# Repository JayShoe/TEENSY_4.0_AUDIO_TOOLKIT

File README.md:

# Teensy 4.0 Audio Toolkit and Shield
Licensed under CC BY-NC-SA 4.0
https://creativecommons.org/licenses/by-nc-sa/4.0/
Project by Jay Shoemaker

*Project is incomplete, accepting feedback now!

The Teensy 4.0 Audio Toolkit and Shield is part of an open source project for learning about, designing, and rapid-prototyping custom Audio PCBs using the Teensy Audio Library. This kit exposes key features of the Teensy commonly used for audio including USB Host Input, MIDI In, Midi Out, Midi Through, SPDIF, and Toslink. The board also includes an SD Memory Card reader, RAM/Memory, and a Power Supply. Plus, the schematic points out the key pins for connecting your own audio chips to the Teensy. This project is just exposing the hardware. Some functions may require additional work on the Teensy Audio Library or your custom code.  

# Teensy Audio Toolkit and Shield's Key Features
 * Open Source CC BY-NC-SA 4.0
 * Stackable Design – To easily integrate with other stackable modules including DAC, ADC, Codec, Bluetooth, etc. 
 * Starting Point for Custom IO Panels – All inputs/outputs are only exposed as header pins. Use of a custom daughterboard, dongle, or soldering directly to the Audio Toolkit Mainboard to expose the desired jacks or ports. 
  * SD Card Reader  - via DM3D-SF Hirose Electric Co Ltd. 
  * Memory – via W25Q128JV, W25Q128FV, or 23LC1024 RAM. 
  * USB Host – via standard pinout USB Header and USB A connector and includes a TPS2055A current limiter chip. 
  * SPDIF Input and Output – via header, Coax, or Toslink.
  * MIDI In, Out, and Through – via header, DIN 5, or 3.5mm 3-pin Mini MIDI and includes an optocoupler (6N137) and a logic gate (74LS00) for proper termination. 
  * Power Supply – 1 Amp regulator for both 5V and 3.3V rails (LM2940) with an input voltage range of 6 V to 26 V. 
 * Footprints, 3d Models, and Schematics included. 
 * SAI Connectivity and Labels. The teensy footprint has been modified to include wide pads and pin information for standard I2S connectivity. Solder wire to those pads for an easy and secure connection to external DAC/ADC/CODEC/ETC. 
  * Master Clock - 100 Ohm resistors installed on MCLK1 and MCLK2 lines for easy connectivity. 
  * i2C - Pull up resistors on board for easy connectivity.
# Daughterboards with Jacks/Ports
The Audio Toolkit Shield’s header allows simple connections to one or more daughter boards. The mainboard and daughter board’s source and gerbers will be publicly available on the project repository. Pre-assembled boards will be made available (when tested/complete). Create your own daughterboard using the toolkit as a starting point. (Be sure to contribute back your modifications!)
## Designing a Custom Daughterboard
1.	Delete unneeded parts including the Audio Toolkit Mainboard. 
2.	Place and route your components. Define your edge cuts. Order your board. 
3.	Connect your customer IO Board to the Audio Toolkit Mainboard IO Header. 
## Audio Toolkit Notes
-	Use pre-built IO boards found within the project’s repository. 
-	Use the “Audio Toolkit IO Header” to stack your custom IO Board on top of the mainboard via the headers. 
-	Use the individual headers to create smaller custom IO Boards and link your project via ribbon cables, etc. 
-	Use the schematic to create your own entirely new custom Audio Toolkit or integrate it into your own project.

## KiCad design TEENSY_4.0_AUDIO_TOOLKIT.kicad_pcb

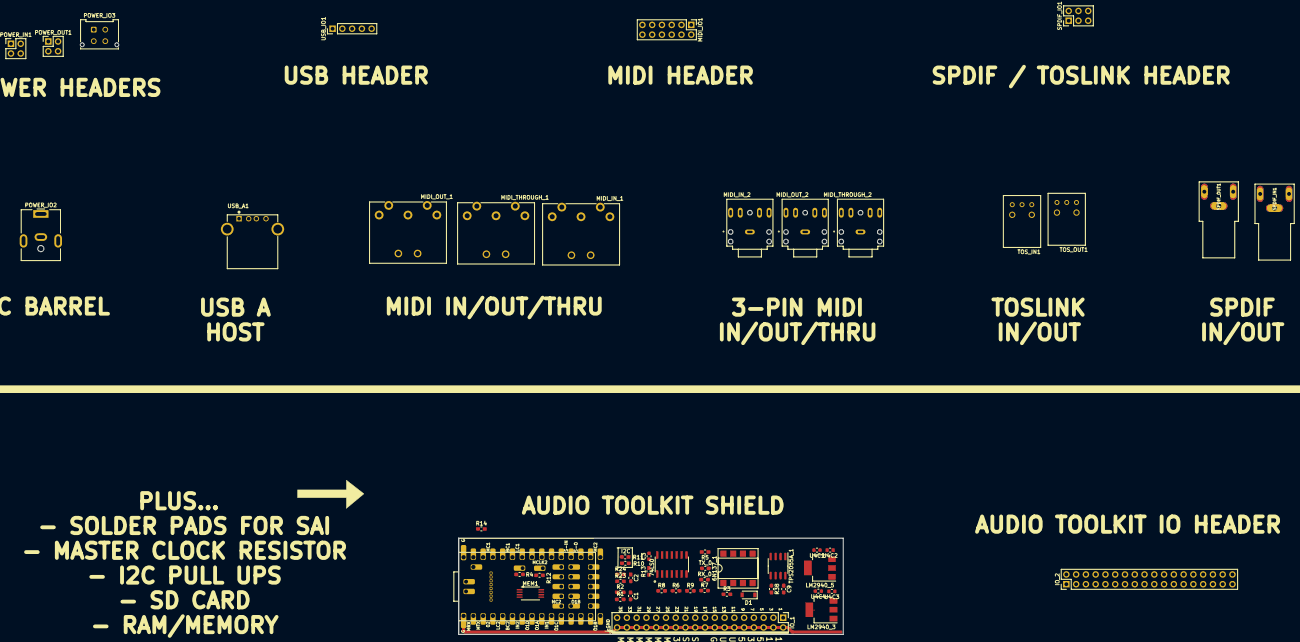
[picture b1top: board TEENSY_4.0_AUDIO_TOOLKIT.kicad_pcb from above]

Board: 2 copper layers, 100.0 x 25.0 mm, 58 parts (1 on the bottom side), 56 nets.

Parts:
6N137_1: 6N137; DIP-8_W7.62mm_SMDSocket_SmallPads
74LS0: 74LS00; 74LS00_SOIC127P600X175-14N
C1, C2: 1μ; C_0603_1608Metric_Pad1.05x0.95mm_HandSolder
C3: .1 uF; C_0603_1608Metric
C9: 100uf; C_0603_1608Metric_Pad1.05x0.95mm_HandSolder
D1: 1N4148; D_SOD-123
IO_1: IO_1; PinHeader_2x18_P2.54mm_Vertical
IO_2: IO_2; PinHeader_2x18_P2.54mm_Vertical
LM2940_3: LM2940IMP-33; SOT-223
LM2940_5: LM2940IMP-5; SOT-223
MCLK1: MCLK1; SolderWirePad_1x01_THROUGH_SOLDER
MCLK2: MCLK2; SolderWirePad_1x01_THROUGH_SOLDER
MEM1: 23LC1024-I_P; 23LC1024
MIDI_IN_1: DIN-5; SDS-50J_MIDI_JACK
MIDI_IN_2: 35RAPC4BHN2; 3.5MM_SWITCHCRAFT_35RAPC4BHN2
MIDI_IO1: MIDI_IO1; PinHeader_2x06_P2.54mm_Vertical
MIDI_OUT_1: DIN-5; SDS-50J_MIDI_JACK
MIDI_OUT_2: 35RAPC4BHN2; 3.5MM_SWITCHCRAFT_35RAPC4BHN2
MIDI_THROUGH_1: DIN-5; SDS-50J_MIDI_JACK
MIDI_THROUGH_2: 35RAPC4BHN2; 3.5MM_SWITCHCRAFT_35RAPC4BHN2
POWER_IN1: Conn_02x02_Odd_Even; PinHeader_2x02_P2.54mm_Vertical
POWER_IO2: Barrel_Jack; BarrelJack_CUI_PJ-063AH_Horizontal
POWER_IO3: Microfit_power; Molex_Micro-Fit_3.0_43045-0412_2x02_P3.00mm_Vertical
POWER_OUT1: Conn_02x02_Odd_Even; PinHeader_2x02_P2.54mm_Vertical
R1, R2, R23, R24: 22; R_0603_1608Metric_Pad1.05x0.95mm_HandSolder
R3, R14: 220R; R_0603_1608Metric_Pad1.05x0.95mm_HandSolder
R4, R12: 100 Ohm; R_0603_1608Metric_Pad1.05x0.95mm_HandSolder
R5: 1K5; R_0603_1608Metric_Pad1.05x0.95mm_HandSolder
R6, R9: 220; R_0603_1608Metric_Pad1.05x0.95mm_HandSolder
R7, R8: 47; R_0603_1608Metric_Pad1.05x0.95mm_HandSolder
R10, R11: 2.2K; R_0603_1608Metric_Pad1.05x0.95mm_HandSolder
R13: 470; R_0603_1608Metric_Pad1.05x0.95mm_HandSolder
R38: 44ohm; R_0603_1608Metric_Pad1.05x0.95mm_HandSolder
RX_0: 0.0; R_0603_1608Metric_Pad1.05x0.95mm_HandSolder
SD1: DM3D-SF-Hirose; DM3D-SF
SPDIF_IN1: PJRAN1X1U04X; SPDIF_PJRAN1X1U01X
SPDIF_IO1: Conn_02x03_Odd_Even; PinHeader_2x03_P2.54mm_Vertical
SPDIF_OUT1: PJRAN1X1U04X; SPDIF_PJRAN1X1U01X
TOS_IN1: EAPLRAA4; PLR135-T10_PLT133-T10W
TOS_OUT1: PLT133-T10W; PLR135-T10_PLT133-T10W
TPS2055A_1: TPS2055A-TPS2055A; SOIC-8_3.9x4.9mm_P1.27mm
TX_0: 0.0; R_0603_1608Metric_Pad1.05x0.95mm_HandSolder
U3: Teensy4.0; Teensy40_SMT_Audio_Kit_2
U4C1, U4C4: 22 uF; C_0603_1608Metric
U4C2, U4C3: 0.47uF; C_0603_1608Metric
USB_A1: USB_A; TE_292303-4
USB_IO1: USB_Header_5_Pin-USB_Header; PinHeader_1x05_P2.54mm_Vertical

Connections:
3.3V: IO_1.7, IO_1.23, LM2940_3.2, MEM1.3, MEM1.7, MEM1.8, R10.2, R11.2, SD1.4, U3.31, U4C4.1
3.3V_H: IO_2.7, IO_2.23, POWER_OUT1.3
5V: 6N137_1.8, 74LS0.14, C3.2, IO_1.5, LM2940_5.2, R6.2, R7.2, TPS2055A_1.2, TPS2055A_1.4, U3.33, U4C1.1
5V_H: IO_2.5, POWER_OUT1.1
5V_TPS2055A: C9.1, IO_1.9, TPS2055A_1.6, TPS2055A_1.7, TPS2055A_1.8
5V_TPS2055A_H: IO_2.9, USB_A1.1, USB_IO1.1
12V: IO_1.1, IO_1.3, LM2940_5.3, U4C2.1
12V_H: IO_2.1, IO_2.3, POWER_IN1.1, POWER_IN1.3, POWER_IO3.1, POWER_IO3.2
GND: 6N137_1.5, 74LS0.7, C3.1, C9.2, IO_1.2, IO_1.4, IO_1.6, IO_1.8, IO_1.10, IO_1.12, IO_1.14, IO_1.15, IO_1.16, IO_1.18, IO_1.20, IO_1.22, IO_1.24, IO_1.26, IO_1.28, IO_1.30, IO_1.32, IO_1.34, IO_1.36, LM2940_3.1, LM2940_5.1, MEM1.4, R2.2, R5.1, R24.2, SD1.6, U3.1, U3.17, U3.32, U4C1.2, U4C2.2, U4C3.2, U4C4.2
GND_H: IO_2.2, IO_2.4, IO_2.6, IO_2.8, IO_2.10, IO_2.12, IO_2.14, IO_2.15, IO_2.16, IO_2.18, IO_2.20, IO_2.22, IO_2.24, IO_2.26, IO_2.28, IO_2.30, IO_2.32, IO_2.34, IO_2.36, MIDI_IN_1.2, MIDI_IN_2.2, MIDI_OUT_1.2, MIDI_OUT_2.2, MIDI_THROUGH_1.2, MIDI_THROUGH_2.2, POWER_IN1.2, POWER_IN1.4, POWER_IO2.2, POWER_IO3.3, POWER_IO3.4, POWER_OUT1.2, POWER_OUT1.4, SPDIF_IN1.1, SPDIF_IO1.2, SPDIF_IO1.4, SPDIF_IO1.6, SPDIF_OUT1.1, TOS_IN1.1, TOS_OUT1.1, USB_A1.4, USB_IO1.4
MCLK1: R4.2, U3.30
MCLK2: R12.2, U3.44
MIDI_IN_4: IO_1.25, R3.1
MIDI_IN_4_H: IO_2.25, MIDI_IN_1.4, MIDI_IN_2.1, MIDI_IO1.1
MIDI_IN_5: 6N137_1.3, D1.2, IO_1.27
MIDI_IN_5_H: IO_2.27, MIDI_IN_1.5, MIDI_IN_2.3, MIDI_IO1.3
MIDI_OUT_4: IO_1.29, R7.1
MIDI_OUT_4_H: IO_2.29, MIDI_IO1.5, MIDI_OUT_1.4, MIDI_THROUGH_2.1
MIDI_OUT_5: IO_1.31, R9.1
MIDI_OUT_5_H: IO_2.31, MIDI_IO1.7, MIDI_OUT_1.5, MIDI_THROUGH_2.3
MIDI_RX: 6N137_1.6, 74LS0.1, 74LS0.2, R13.2, RX_0.2, U3.2
MIDI_THRU_4: IO_1.33, R6.1
MIDI_THRU_4_H: IO_2.33, MIDI_IO1.9, MIDI_OUT_2.1, MIDI_THROUGH_1.4
MIDI_THRU_5: IO_1.35, R8.1
MIDI_THRU_5_H: IO_2.35, MIDI_IO1.11, MIDI_OUT_2.3, MIDI_THROUGH_1.5
MIDI_TX: 74LS0.12, 74LS0.13, TX_0.2, U3.3
unnamed: 6N137_1.2, D1.1, R3.2
unnamed: 6N137_1.7, R5.2
unnamed: 74LS0.3, 74LS0.4, 74LS0.5
unnamed: 74LS0.6, R9.2, RX_0.1
unnamed: 74LS0.8, R8.2, TX_0.1
unnamed: 74LS0.9, 74LS0.10, 74LS0.11
unnamed: C1.2, R1.2
unnamed: C2.2, R23.2
unnamed: MCLK1.1, R4.1
unnamed: MCLK2.1, R12.1
unnamed: R38.2, TPS2055A_1.5
OUT1B: R14.1, U3.43
SCL0: R10.1, U3.26
SDA0: R11.1, U3.25
SD_CLK: SD1.5, U3.48
SD_CMD: SD1.3, U3.50
SD_DAT0: SD1.7, U3.46
SD_DAT1: SD1.8, U3.45
SD_DAT2: SD1.1, U3.52
SD_DAT3: SD1.2, U3.51
SPDIF_3.3V_H: SPDIF_IO1.5, TOS_IN1.2, TOS_OUT1.2
SPDIF_IN: C1.1, IO_1.21, R1.1, R2.1
SPDIF_IN_H: IO_2.21, SPDIF_IN1.2, SPDIF_IO1.3, TOS_IN1.3
SPDIF_OUT: C2.1, IO_1.19, R23.1, R24.1
SPDIF_OUT_H: IO_2.19, SPDIF_IO1.1, SPDIF_OUT1.2, TOS_OUT1.3
USB_D+: IO_1.13, U3.54
USB_D+_H: IO_2.13, USB_A1.3, USB_IO1.3
USB_D-: IO_1.11, U3.53
USB_D-_H: IO_2.11, USB_A1.2, USB_IO1.2
VIN: LM2940_3.3, U4C3.1

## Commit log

2020-04-11 Added images
2020-04-11 Update image
2020-04-11 Updated Image
2020-04-11 Updated images.
2020-04-12 Added SAI Expansion Headers
2020-04-13 Added labels to IO
2020-04-14 Update TEENSY_4.0_AUDIO_TOOLKIT.sch
    MCLK2 was on the wrong pin.

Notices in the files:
parts and their libraries:
Copyright 2016 Accelerated Designs. All rights reserved.
